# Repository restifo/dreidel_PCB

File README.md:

# Dreidel Controller
This is a KiCad project for a custom dreidel controller. It should be used with the Arduino
sketch repository.

WARNING! This project uses line voltage (120V) to drive rope lights or other similar non-LED
lighting. Use at your own risk. There is a risk of electrocution or death when using
mains voltage. Do not use this project if you're unaware of the issues involved.

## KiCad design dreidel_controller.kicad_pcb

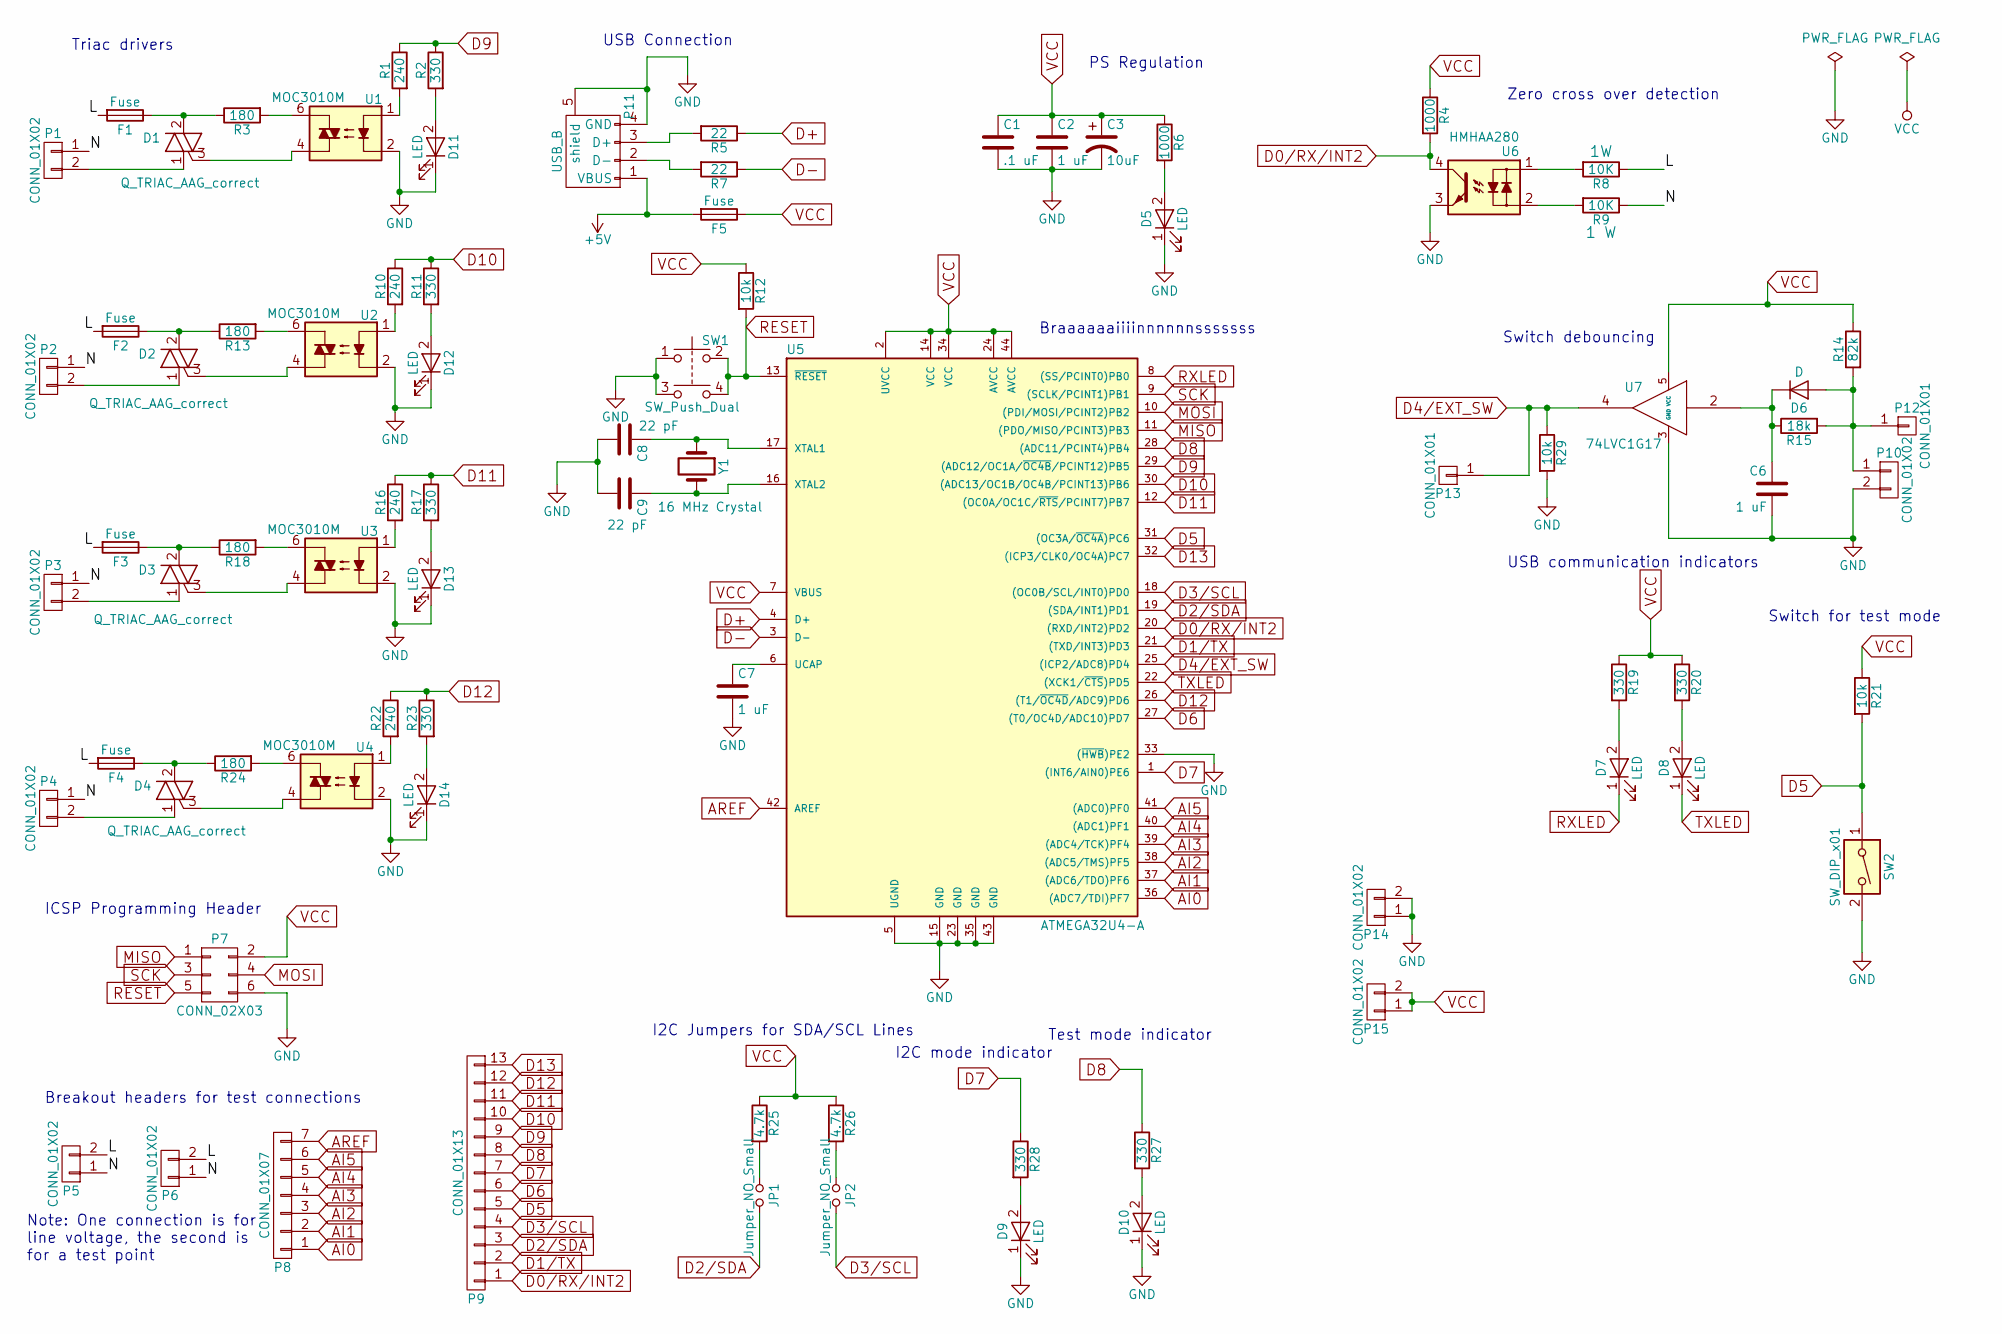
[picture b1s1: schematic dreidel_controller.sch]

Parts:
C1: .1 uF; C_1206
C2, C6, C7: 1 uF; C_1206
C3: 10uF; C_1206
C8, C9: 22 pF; C_1206
D1, D2, D3, D4: Q_TRIAC_AAG_correct; TO-220_Vertical
D5, D7, D8, D9, D10, D11, D12, D13, D14: LED; LED_1206
D6: D; D_SOD-123
F1, F2, F3, F4: Fuse; Fuseholder5x20_horiz_open_lateral_Type-II
F5: Fuse; Fuse_SMD2920
JP1, JP2: Jumper_NO_Small; Pin_Header_Straight_1x02_Pitch2.54mm
P1, P2, P3, P4, P5, P6: CONN_01X02; PhoenixContact_MCV-G_02x3.50mm_Vertical
P7: CONN_02X03; IDC_Header_Straight_6pins
P8: CONN_01X07; Socket_Strip_Straight_1x07
P9: CONN_01X13; Socket_Strip_Straight_1x13
P10: CONN_01X02; Socket_Strip_Straight_1x02
P11: USB_B; USB_Micro-B
P12, P13: CONN_01X01; Socket_Strip_Straight_1x01_Pitch2.54mm
P14, P15: CONN_01X02; Socket_Strip_Straight_2x01_Pitch2.54mm
R1, R10, R16, R22: 240; R_1206
R2, R11, R17, R19, R20, R23, R27, R28: 330; R_1206
R3, R13, R18, R24: 180; R_1206
R4, R6: 1000; R_1206
R5, R7: 22; R_1206
R8, R9: 10K; R_2010
R12, R21, R29: 10k; R_1206
R14: 82k; R_1206
R15: 18k; R_1206
R25, R26: 4.7k; R_1206
SW1: SW_Push_Dual; SW_SPST_B3S-1000
SW2: SW_DIP_x01; SW_DIP_x1_W7.62mm_Slide
U1, U2, U3, U4: MOC3010M; DIP-6_W7.62mm_SMD-MOC3010M-Correct
U5: ATMEGA32U4-A; TQFP-44_10x10mm_Pitch0.8mm
U6: HMHAA280; SOP-4
U7: 74LVC1G17; SOT-353_SC-70-5_Handsoldering
Y1: 16 MHz Crystal; Crystal_SMD_HC49-SD

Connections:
+5V: F5.2, P11.1 (VBUS)
/L: F1.2, F2.2, F3.2, F4.2, P5.2, P6.2, R8.1
/N: P1.1, P2.1, P3.1, P4.1, P5.1, P6.1, R9.1
AI0: P8.1, U5.36 ((ADC7/TDI)PF7)
AI1: P8.2, U5.37 ((ADC6/TDO)PF6)
AI2: P8.3, U5.38 ((ADC5/TMS)PF5)
AI3: P8.4, U5.39 ((ADC4/TCK)PF4)
AI4: P8.5, U5.40 ((ADC1)PF1)
AI5: P8.6, U5.41 ((ADC0)PF0)
AREF: P8.7, U5.42 (AREF)
D0/RX/INT2: P9.1, R4.2, U5.20 ((RXD/INT2)PD2), U6.4
D1/TX: P9.2, U5.21 ((TXD/INT3)PD3)
D2/SDA: JP1.2, P9.3, U5.19 ((SDA/INT1)PD1)
D3/SCL: JP2.2, P9.4, U5.18 ((OC0B/SCL/INT0)PD0)
D4/EXT_SW: P13.1, R29.1, U5.25 ((ICP2/ADC8)PD4), U7.4
D5: P9.5, R21.2, SW2.1, U5.31 ((OC3A/~OC4A~)PC6)
D6: P9.6, U5.27 ((T0/OC4D/ADC10)PD7)
D7: P9.7, R28.1, U5.1 ((INT6/AIN0)PE6)
D8: P9.8, R27.1, U5.28 ((ADC11/PCINT4)PB4)
D9: P9.9, R1.1, R2.1, U5.29 ((ADC12/OC1A/~OC4B~/PCINT12)PB5)
D10: P9.10, R10.1, R11.1, U5.30 ((ADC13/OC1B/OC4B/PCINT13)PB6)
D11: P9.11, R16.1, R17.1, U5.12 ((OC0A/OC1C/~RTS~/PCINT7)PB7)
D12: P9.12, R22.1, R23.1, U5.26 ((T1/~OC4D~/ADC9)PD6)
D13: P9.13, U5.32 ((ICP3/CLK0/OC4A)PC7)
D+: R5.1, U5.4 (D+)
D-: R7.1, U5.3 (D-)
GND: C1.2, C2.2, C3.2, C6.2, C7.2, C8.2, C9.2, D5.1 (K), D9.1 (K), D10.1 (K), D11.1 (K), D12.1 (K), D13.1 (K), D14.1 (K), P7.6, P10.2, P11.4 (GND), P11.5 (shield), P14.1, P14.2, R29.2, SW1.1, SW1.3, SW2.2, U1.2, U2.2, U3.2, U4.2, U5.5 (UGND), U5.15 (GND), U5.23 (GND), U5.33 ((~HWB~)PE2), U5.35 (GND), U5.43 (GND), U6.3, U7.3 (GND)
MISO: P7.1, U5.11 ((PDO/MISO/PCINT3)PB3)
MOSI: P7.4, U5.10 ((PDI/MOSI/PCINT2)PB2)
unnamed: C6.1, D6.1 (K), R15.1, U7.2
unnamed: C7.1, U5.6 (UCAP)
unnamed: C8.1, U5.17 (XTAL1), Y1.1
unnamed: C9.1, U5.16 (XTAL2), Y1.2
unnamed: D1.1 (A1), P1.2
unnamed: D1.2 (A2), F1.1, R3.1
unnamed: D1.3 (G), U1.4
unnamed: D2.1 (A1), P2.2
unnamed: D2.2 (A2), F2.1, R13.1
unnamed: D2.3 (G), U2.4
unnamed: D3.1 (A1), P3.2
unnamed: D3.2 (A2), F3.1, R18.1
unnamed: D3.3 (G), U3.4
unnamed: D4.1 (A1), P4.2
unnamed: D4.2 (A2), F4.1, R24.1
unnamed: D4.3 (G), U4.4
unnamed: D5.2 (A), R6.2
unnamed: D6.2 (A), P10.1, P12.1, R14.2, R15.2
unnamed: D7.2 (A), R19.2
unnamed: D8.2 (A), R20.2
unnamed: D9.2 (A), R28.2
unnamed: D10.2 (A), R27.2
unnamed: D11.2 (A), R2.2
unnamed: D12.2 (A), R11.2
unnamed: D13.2 (A), R17.2
unnamed: D14.2 (A), R23.2
unnamed: JP1.1, R25.2
unnamed: JP2.1, R26.2
unnamed: P11.2 (D-), R7.2
unnamed: P11.3 (D+), R5.2
unnamed: R1.2, U1.1
unnamed: R3.2, U1.6
unnamed: R8.2, U6.1
unnamed: R9.2, U6.2
unnamed: R10.2, U2.1
unnamed: R13.2, U2.6
unnamed: R16.2, U3.1
unnamed: R18.2, U3.6
unnamed: R22.2, U4.1
unnamed: R24.2, U4.6
RESET: P7.5, R12.2, SW1.2, SW1.4, U5.13 (~RESET~)
RXLED: D7.1 (K), U5.8 ((SS/PCINT0)PB0)
SCK: P7.3, U5.9 ((SCLK/PCINT1)PB1)
TXLED: D8.1 (K), U5.22 ((XCK1/~CTS~)PD5)
VCC: C1.1, C2.1, C3.1, F5.1, P7.2, P15.1, P15.2, R4.1, R6.1, R12.1, R14.1, R19.1, R20.1, R21.1, R25.1, R26.1, U5.2 (UVCC), U5.7 (VBUS), U5.14 (VCC), U5.24 (AVCC), U5.34 (VCC), U5.44 (AVCC), U7.5 (VCC)

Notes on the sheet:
ICSP Programming Header
I2C Jumpers for SDA/SCL Lines
Breakout headers for test connections
USB Connection
Triac drivers
PS Regulation
Zero cross over detection
Switch debouncing
USB communication indicators
Switch for test mode
Braaaaaaiiiinnnnnnsssssss
Note: One connection is for line voltage, the second is for a test point
Test mode indicator
I2C mode indicator

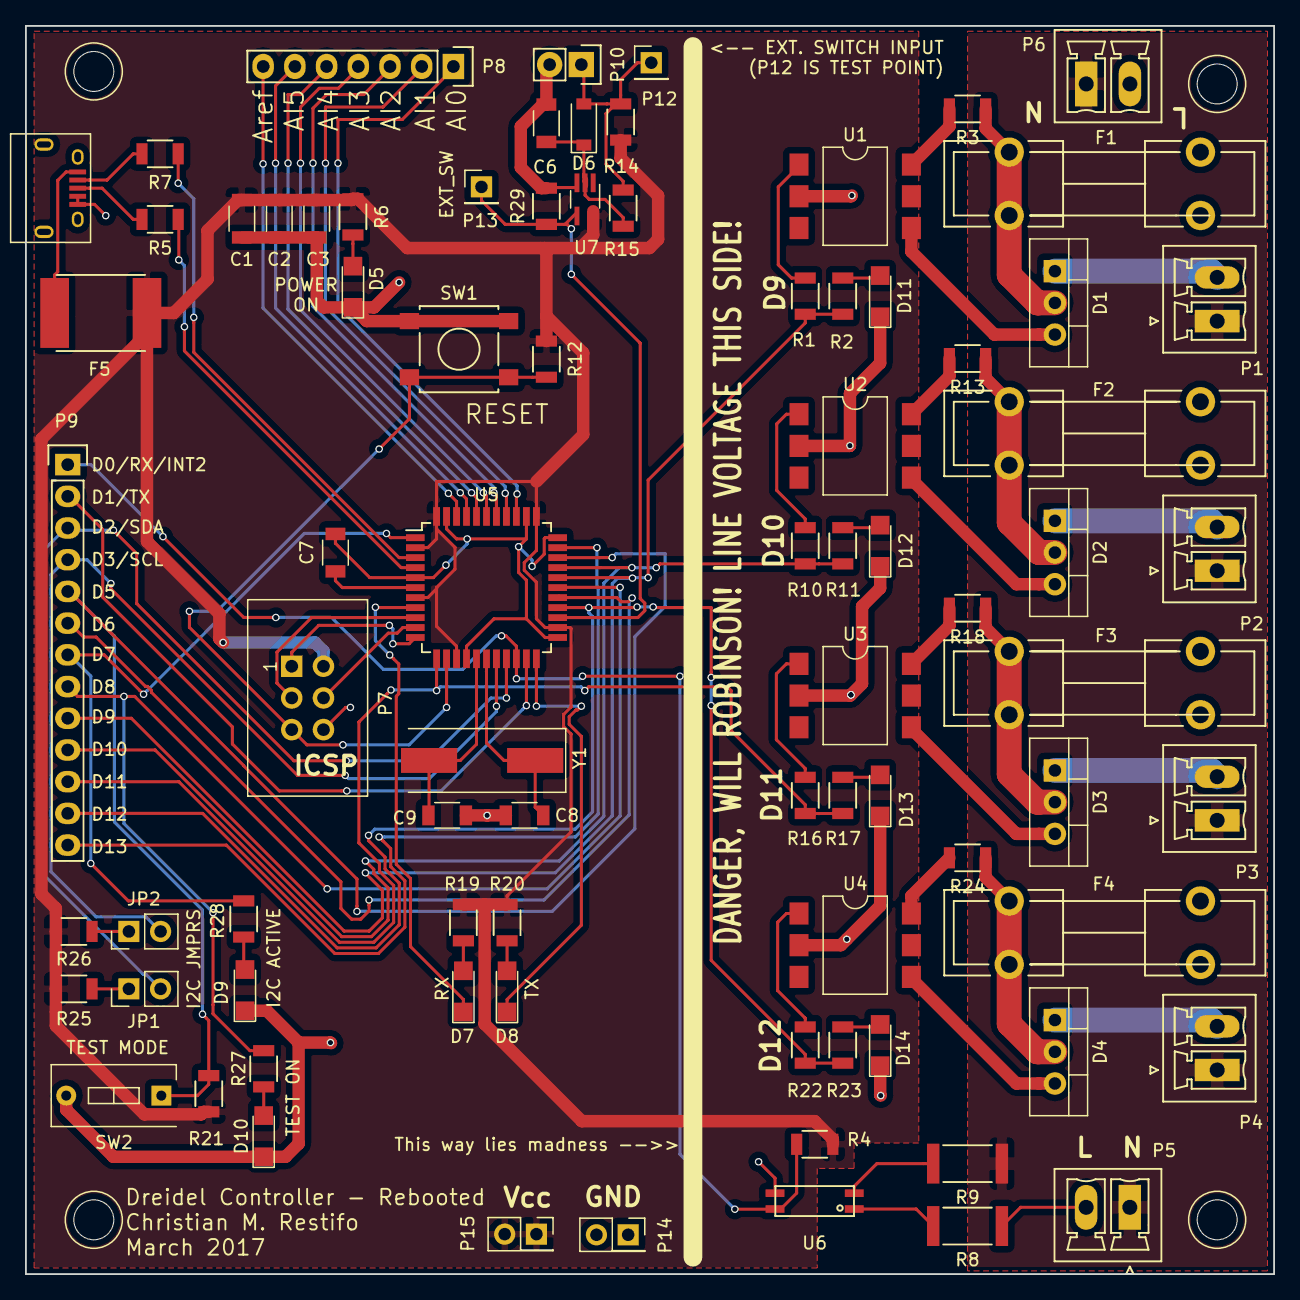
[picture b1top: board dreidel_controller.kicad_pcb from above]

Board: 2 copper layers, 100.0 x 100.0 mm, 82 parts (0 on the bottom side), 74 nets.
